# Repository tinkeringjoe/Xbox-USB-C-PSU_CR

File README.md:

This fork is for the following:

1) Reducing cost by using a cheap single IC that requires barely any supporting passives for USB-PD negotiating.
2) Updating power good signal to be an AND of the 4 power rails rather than a wired OR for power good.
3) Move components from back to front to simplify manufacturing.
4) Change from solder pads to through holes for power cabling; add enough holes for all XBOX revisions cabling.

Goals 1-4 completed. Additionally changed the following.
Inductor/output capacitors for all power rails have been updated per datasheet equations to minimize ripple.
Cost reduced components (BOM will remain hidden until testing is completed.)

This board supports the following power on the rails with an expected ripple of around 1%
5V - 15A
12V - 1.5A
3.3V - 5A
3.3VSB - 700mA

5 turn-key boards have been ordered to test. The following testing is to occur before even touching an XBOX.

1.) Power supply ripple is to be measured under the following conditions (1%, 25%, 50%, 100% of peak load). Should not exeed 5%.
2.) Load removal testing; 100% to 0% load. Should not exceed 10% of voltage rail.

Once these requirements have been satisfied real-hardware testing can occur.

# Xbox-USB-C-PSU
The first ever USB C PSU for the original Xbox

# NOTE:
This board currently supports all 3 Xbox motherboard revisions, but requires a different BOM for 009 and 012 than 121.
If you don't know what revision your Xbox is, you can find out with this guide: [https://www.herringhardware.com/xboxrevisions](https://www.herringhardware.com/XboxRevisions.html)

# REPO STRUCTURE:
All source files for the PCB are contained within the respective folder for each of the 3 official Xbox PCB revions,
-121 to start with, and -009 and -012 will be added soon.
Production files to manufacture the PCBs are located in [Releases](https://github.com/Redherring32/Xbox-USB-C-PSU/releases)

# PCB SPECS:
* 4 layers
* 151.739x39.78mm
* 1oz copper (all layers), heat issues may result from skimping on this
* filled vias (VIPPO) for assembly reasons due to via in pad

## LICENSE:
Licensed under
the TAPR Open hardware license (www.tapr.org/OHL)

©Redherring32 2025

## DISCLAIMER:
I offer this with no warranty, express or implied, and I am NOT responsible for anything that may happen as a result of misuse of this PCB.
You have been warned.

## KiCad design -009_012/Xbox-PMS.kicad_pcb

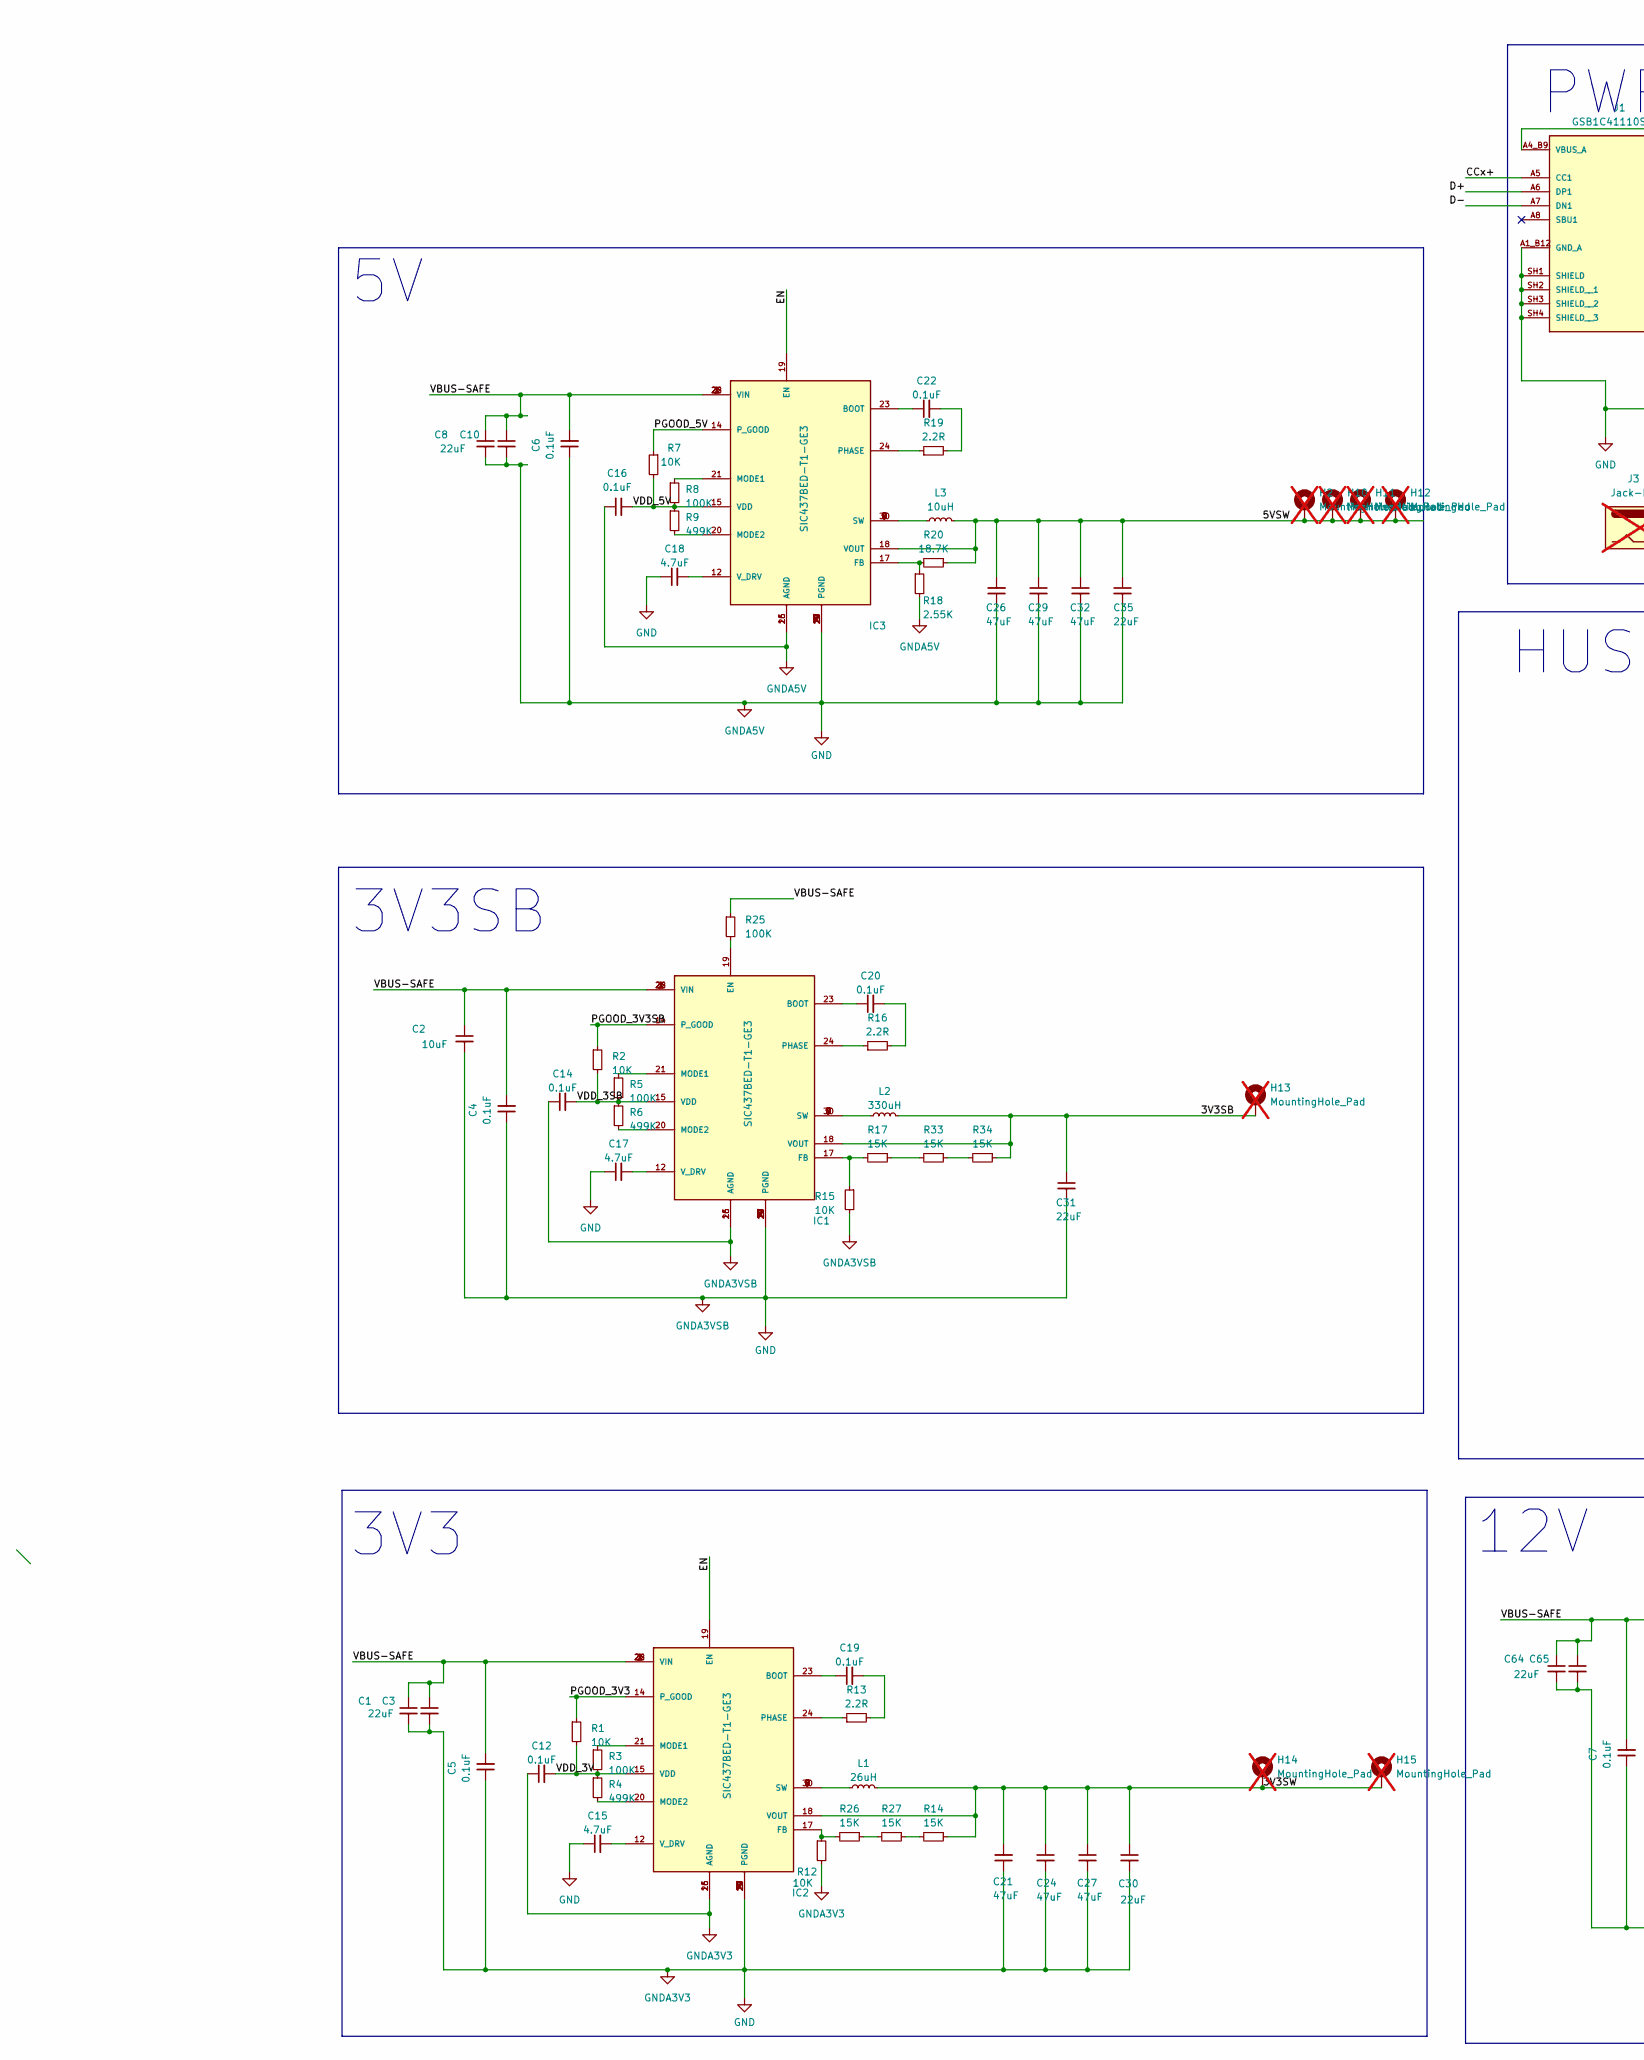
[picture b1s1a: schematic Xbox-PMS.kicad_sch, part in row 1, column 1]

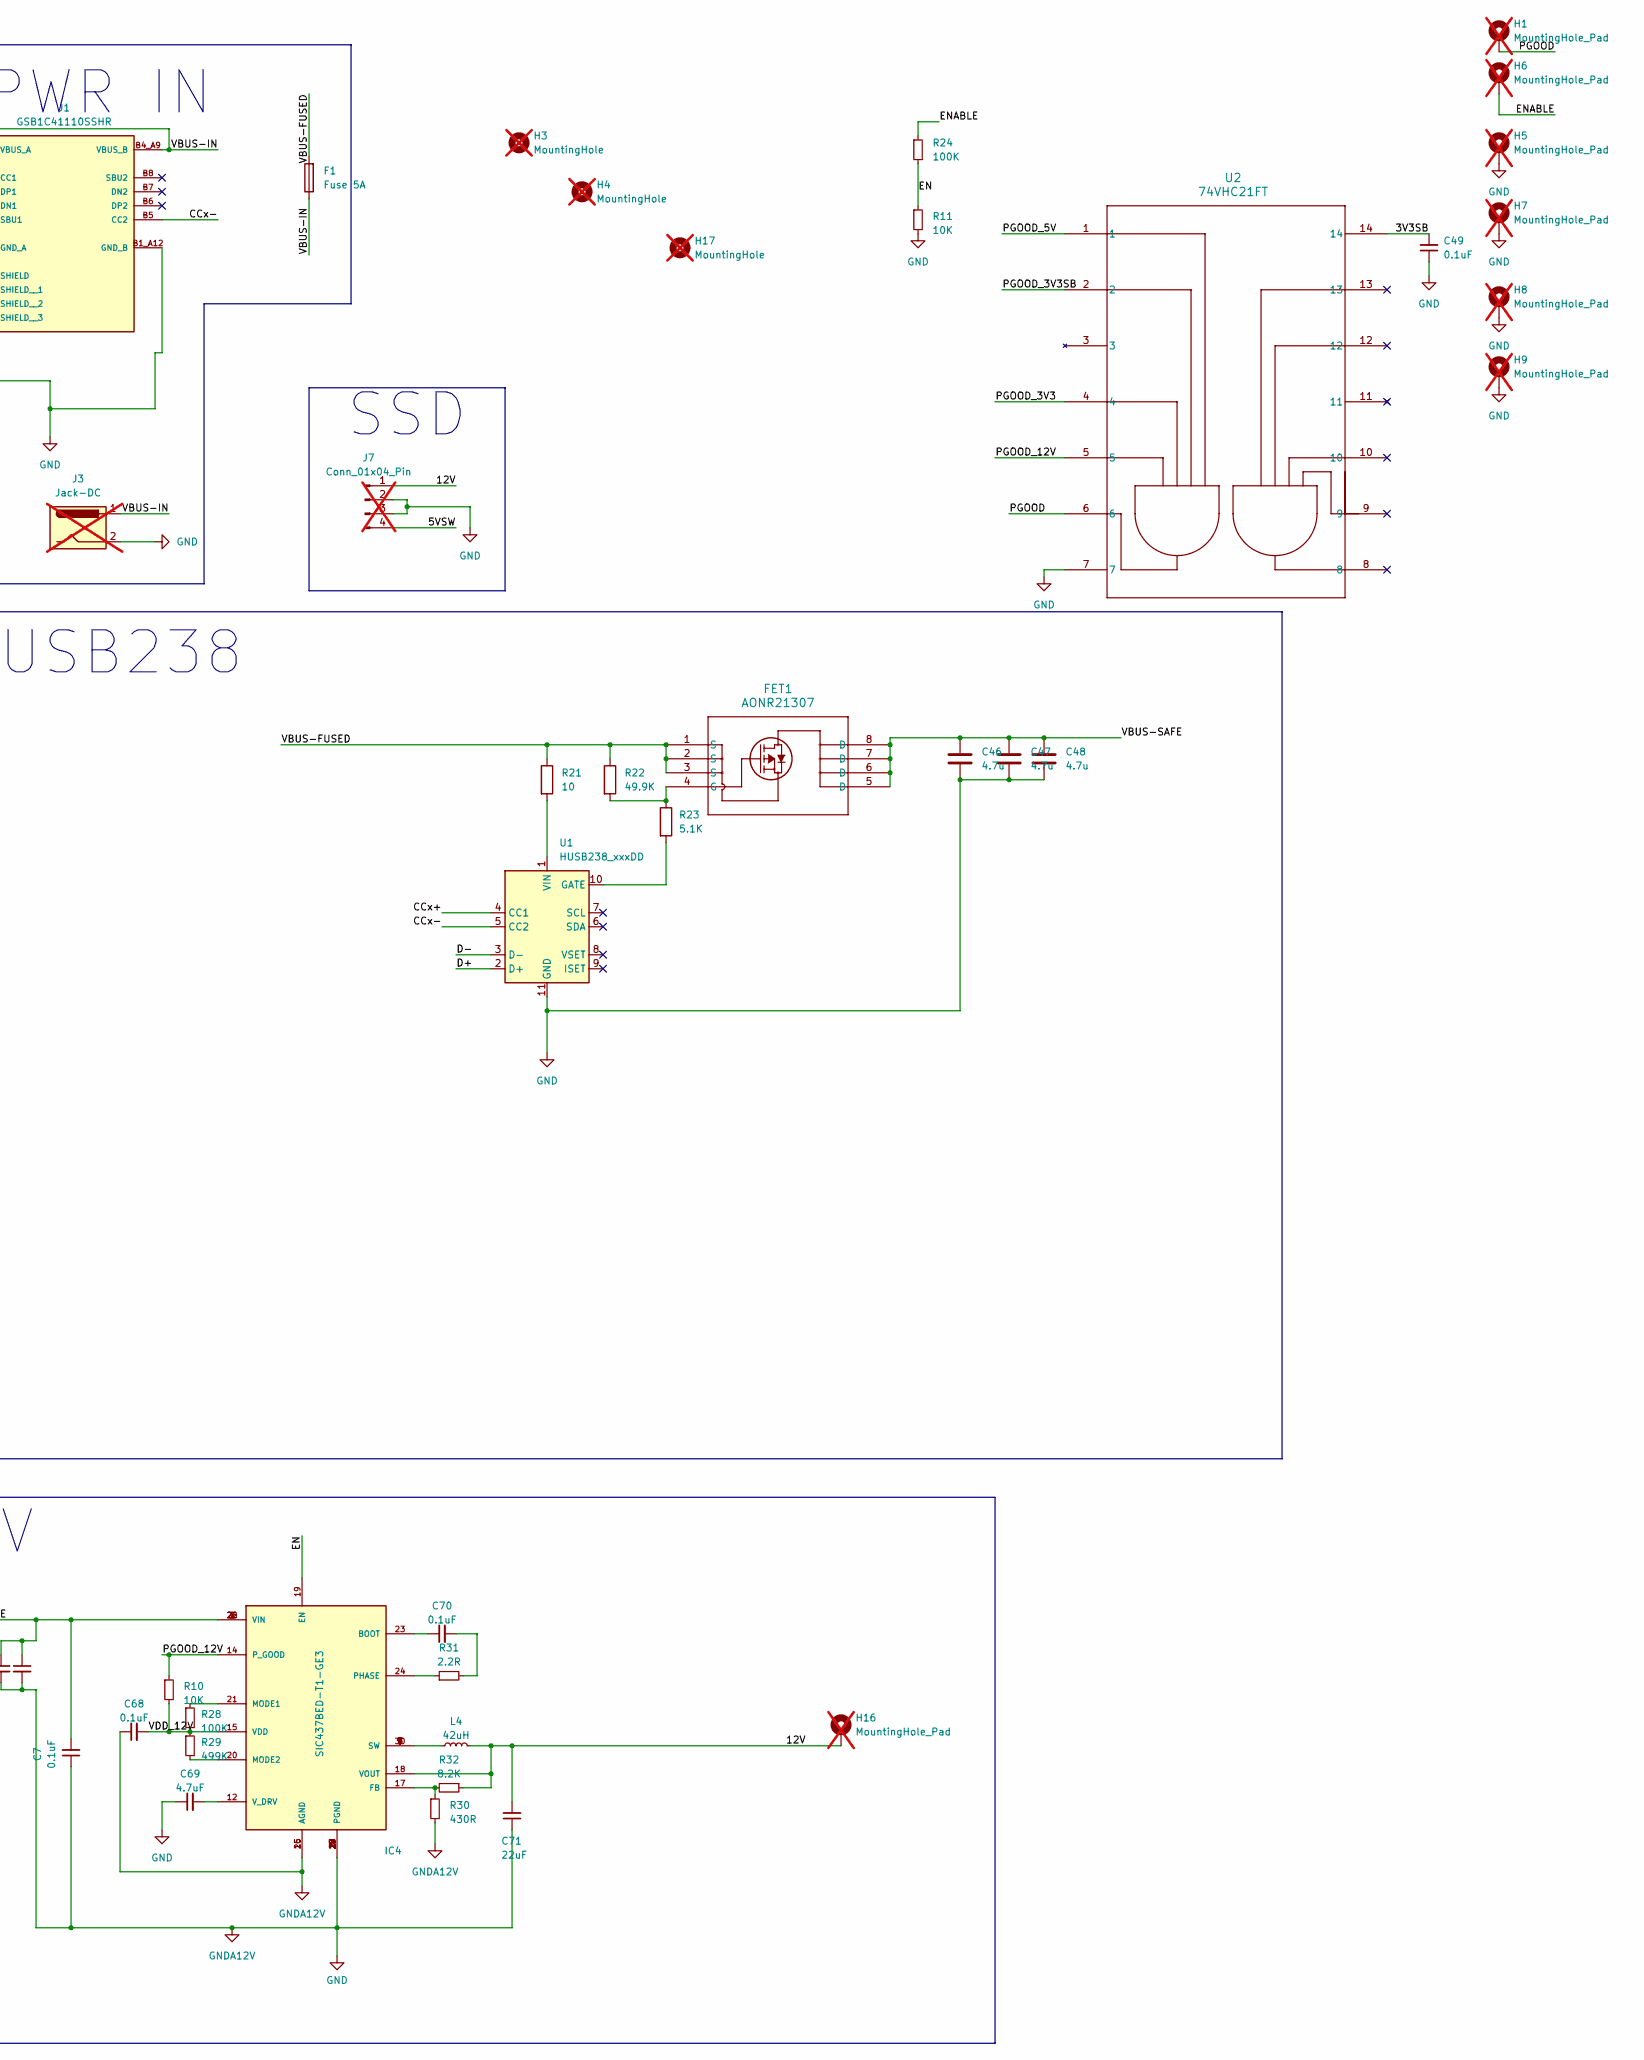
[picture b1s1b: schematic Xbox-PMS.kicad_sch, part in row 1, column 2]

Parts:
C1, C3, C8, C10, C64, C65: 22uF; C_1210_3225Metric
C2: 10uF; C_1210_3225Metric
C4, C5, C6, C7, C12, C14, C16, C19, C20, C22, C49, C68, C70: 0.1uF; C_0402_1005Metric
C15, C17, C18, C69: 4.7uF; C_0603_1608Metric
C21, C24, C26, C27, C29, C32: 47uF; C_1210_3225Metric
C30, C31, C35: 22uF; C_0603_1608Metric
C46, C47, C48: 4.7u; C_1210_3225Metric
C71: 22uF; R_0805_2012Metric
F1: Fuse 5A; Fuse_2512_6332Metric
FET1: AONR21307; DFN8_3x3_EP_AOS
H1, H2, H5, H6, H7, H8, H9, H10, H11, H12, H13, H14, H15, H16: MountingHole_Pad; TestPoint_THTPad_2.5x2.5mm_Drill1.2mm; not fitted
H3, H4, H17: MountingHole; MountingHole_2.2mm_M2; not fitted
IC1, IC2, IC3, IC4: SIC437BED-T1-GE3; SIC437BEDT1GE3
J1: GSB1C41110SSHR; AMPHENOL_GSB1C41110SSHR; PARTREV AX1
J3: Jack-DC; BarrelJack_CUI_PJ-063AH_Horizontal; not fitted
J7: Conn_01x04_Pin; FDD Connector; not fitted
L1: 26uH; fch1350-270M
L2: 330uH; IND_SRN8040TA-331M
L3: 10uH; MDA1870-100M
L4: 42uH; IND_ETQ-P4M470KFM_PAN
R1, R2, R7, R10, R11, R12, R15: 10K; R_0402_1005Metric
R3, R5, R8, R24, R25, R28: 100K; R_0402_1005Metric
R4, R6, R9, R29: 499K; R_0402_1005Metric
R13, R16, R19, R31: 2.2R; R_0402_1005Metric
R14, R17, R26, R27, R33, R34: 15K; R_0402_1005Metric
R18: 2.55K; R_0402_1005Metric
R20: 18.7K; R_0402_1005Metric
R21: 10; R_0402_1005Metric
R22: 49.9K; R_0402_1005Metric
R23: 5.1K; R_0402_1005Metric
R30: 430R; R_0402_1005Metric
R32: 8.2K; R_0402_1005Metric
U1: HUSB238_xxxDD; WDFN-10-1EP_3x3mm_P0.5mm_EP1.8x2.5mm
U2: 74VHC21FT; TSSOP14B_TOS

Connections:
/3V3SB: C31.1, C49.2, H13.1, IC1.18 (VOUT), L2.2, R34.1, U2.14
/3V3SW: C21.2, C24.1, C27.1, C30.1, H14.1, H15.1, IC2.18 (VOUT), L1.2, R14.1
/5VSW: C26.2, C29.1, C32.1, C35.1, H2.1, H10.1, H11.1, H12.1, IC3.18 (VOUT), J7.4, L3.2, R20.1
/12V: C71.2, H16.1, IC4.18 (VOUT), J7.1, L4.2, R32.1
/CCx+: J1.A5 (CC1), U1.4 (CC1)
/CCx-: J1.B5 (CC2), U1.5 (CC2)
/D+: J1.A6 (DP1), U1.2 (D+)
/D-: J1.A7 (DN1), U1.3 (D-)
/EN: IC2.19 (EN), IC3.19 (EN), IC4.19 (EN), R11.1, R24.2
/ENABLE: H6.1, R24.1
/PGOOD: H1.1, U2.6
/PGOOD_3V3: IC2.14 (P_GOOD), R1.1, U2.4
/PGOOD_3V3SB: IC1.14 (P_GOOD), R2.1, U2.2
/PGOOD_5V: IC3.14 (P_GOOD), R7.1, U2.1
/PGOOD_12V: IC4.14 (P_GOOD), R10.1, U2.5
/VBUS-FUSED: F1.2, FET1.1 (S), FET1.2 (S), FET1.3 (S), R21.1, R22.1
/VBUS-IN: F1.1, J1.A4_B9 (VBUS_A), J1.B4_A9 (VBUS_B), J3.1
/VBUS-SAFE: C1.1, C2.1, C3.1, C4.2, C5.2, C6.2, C7.2, C8.1, C10.1, C46.1, C47.1, C48.1, C64.1, C65.1, FET1.5 (D), FET1.6 (D), FET1.7 (D), FET1.8 (D), IC1.1 (VIN), IC1.2 (VIN), IC1.22 (VIN), IC1.26 (VIN), IC2.1 (VIN), IC2.2 (VIN), IC2.22 (VIN), IC2.26 (VIN), IC3.1 (VIN), IC3.2 (VIN), IC3.22 (VIN), IC3.26 (VIN), IC4.1 (VIN), IC4.2 (VIN), IC4.22 (VIN), IC4.26 (VIN), R25.1
/VDD_3SB: C14.2, IC1.15 (VDD), R2.2, R5.2, R6.1
/VDD_3V: C12.2, IC2.15 (VDD), R1.2, R3.2, R4.1
/VDD_5V: C16.2, IC3.15 (VDD), R7.2, R8.2, R9.1
/VDD_12V: C68.2, IC4.15 (VDD), R10.2, R28.2, R29.1
GND: C1.2, C2.2, C3.2, C4.1, C5.1, C6.1, C7.1, C8.2, C10.2, C12.1, C14.1, C15.1, C16.1, C17.1, C18.1, C21.1, C24.2, C26.1, C27.2, C29.2, C30.2, C31.2, C32.2, C35.2, C46.2, C47.2, C48.2, C49.1, C64.2, C65.2, C68.1, C69.1, C71.1, H5.1, H7.1, H8.1, H9.1, IC1.3 (PGND), IC1.4 (PGND), IC1.13 (PGND), IC1.16 (AGND), IC1.25 (AGND), IC1.27 (PGND), IC1.29 (PGND), IC2.3 (PGND), IC2.4 (PGND), IC2.13 (PGND), IC2.16 (AGND), IC2.25 (AGND), IC2.27 (PGND), IC2.29 (PGND), IC3.3 (PGND), IC3.4 (PGND), IC3.13 (PGND), IC3.16 (AGND), IC3.25 (AGND), IC3.27 (PGND), IC3.29 (PGND), IC4.3 (PGND), IC4.4 (PGND), IC4.13 (PGND), IC4.16 (AGND), IC4.25 (AGND), IC4.27 (PGND), IC4.29 (PGND), J1.A1_B12 (GND_A), J1.B1_A12 (GND_B), J1.SH1 (SHIELD), J1.SH2 (SHIELD__1), J1.SH3 (SHIELD__2), J1.SH4 (SHIELD__3), J3.2, J7.2, J7.3, R11.2, R12.2, R15.2, R18.2, R30.2, U1.11 (GND), U2.7
unnamed: C19.2, R13.2
unnamed: C20.2, R16.2
unnamed: C22.2, R19.2
unnamed: C70.2, R31.2
unnamed: FET1.4 (G), R22.2, R23.1
unnamed: C20.1, IC1.23 (BOOT)
unnamed: IC1.19 (EN), R25.2
unnamed: IC1.17 (FB), R15.1, R17.2
unnamed: IC1.21 (MODE1), R5.1
unnamed: IC1.20 (MODE2), R6.2
unnamed: IC1.24 (PHASE), R16.1
unnamed: IC1.5 (SW), IC1.6 (SW), IC1.7 (SW), IC1.8 (SW), IC1.9 (SW), IC1.30 (SW), L2.1
unnamed: C17.2, IC1.12 (V_DRV)
unnamed: C19.1, IC2.23 (BOOT)
unnamed: IC2.17 (FB), R12.1, R26.2
unnamed: IC2.21 (MODE1), R3.1
unnamed: IC2.20 (MODE2), R4.2
unnamed: IC2.24 (PHASE), R13.1
unnamed: IC2.5 (SW), IC2.6 (SW), IC2.7 (SW), IC2.8 (SW), IC2.9 (SW), IC2.30 (SW), L1.1
unnamed: C15.2, IC2.12 (V_DRV)
unnamed: C22.1, IC3.23 (BOOT)
unnamed: IC3.17 (FB), R18.1, R20.2
unnamed: IC3.21 (MODE1), R8.1
unnamed: IC3.20 (MODE2), R9.2
unnamed: IC3.24 (PHASE), R19.1
unnamed: IC3.5 (SW), IC3.6 (SW), IC3.7 (SW), IC3.8 (SW), IC3.9 (SW), IC3.30 (SW), L3.1
unnamed: C18.2, IC3.12 (V_DRV)
unnamed: C70.1, IC4.23 (BOOT)
unnamed: IC4.17 (FB), R30.1, R32.2
unnamed: IC4.21 (MODE1), R28.1
unnamed: IC4.20 (MODE2), R29.2
unnamed: IC4.24 (PHASE), R31.1
unnamed: IC4.5 (SW), IC4.6 (SW), IC4.7 (SW), IC4.8 (SW), IC4.9 (SW), IC4.30 (SW), L4.1
unnamed: C69.2, IC4.12 (V_DRV)
unnamed: R14.2, R27.1
unnamed: R17.1, R33.2
unnamed: R26.1, R27.2
unnamed: R33.1, R34.2
unnamed: R23.2, U1.10 (GATE)
unnamed: R21.2, U1.1 (VIN)

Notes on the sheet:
PWR IN
3V3
12V
3V3SB
SSD
HUSB238

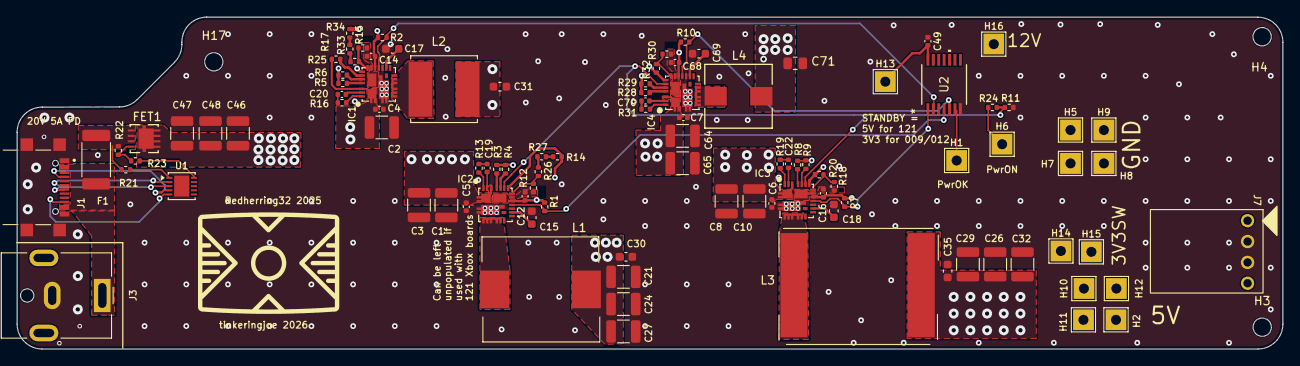
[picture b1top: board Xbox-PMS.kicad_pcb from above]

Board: 4 copper layers, 151.7 x 39.8 mm, 103 parts (0 on the bottom side), 63 nets.

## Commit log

2026-03-03 Update README with fork objectives
    Added details about the purpose and goals of the fork.
2026-03-06 Initial Changes
    Updates for the following:
    1.) Updated all inductor and capacitance values per equations in datasheet. Should minimize power supply ripple and minimize part cost.
    2.) Added AND gate for power good output
    3.) Rerouted board for simplicity and noise isolation.
2026-03-06 Revise README with goals and testing details
    Updated README with completed goals and testing requirements for power supply.
